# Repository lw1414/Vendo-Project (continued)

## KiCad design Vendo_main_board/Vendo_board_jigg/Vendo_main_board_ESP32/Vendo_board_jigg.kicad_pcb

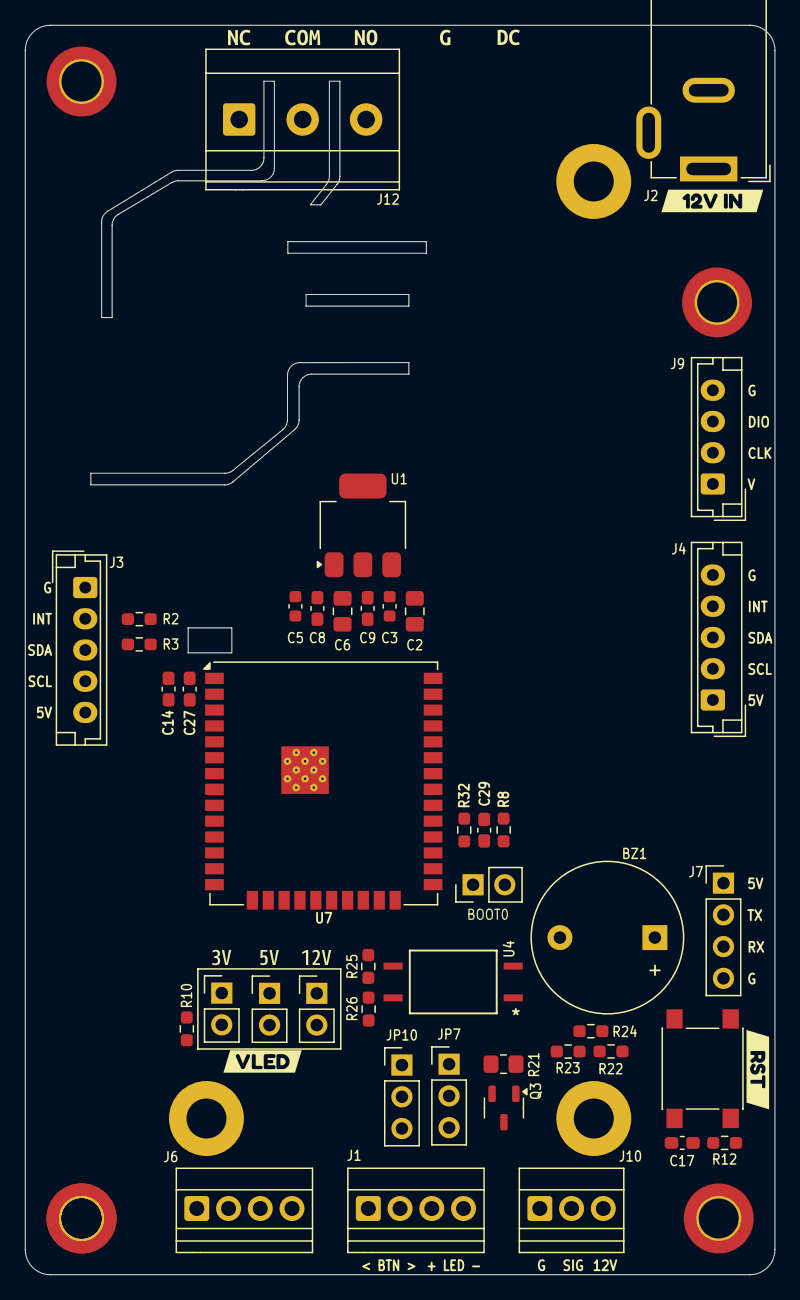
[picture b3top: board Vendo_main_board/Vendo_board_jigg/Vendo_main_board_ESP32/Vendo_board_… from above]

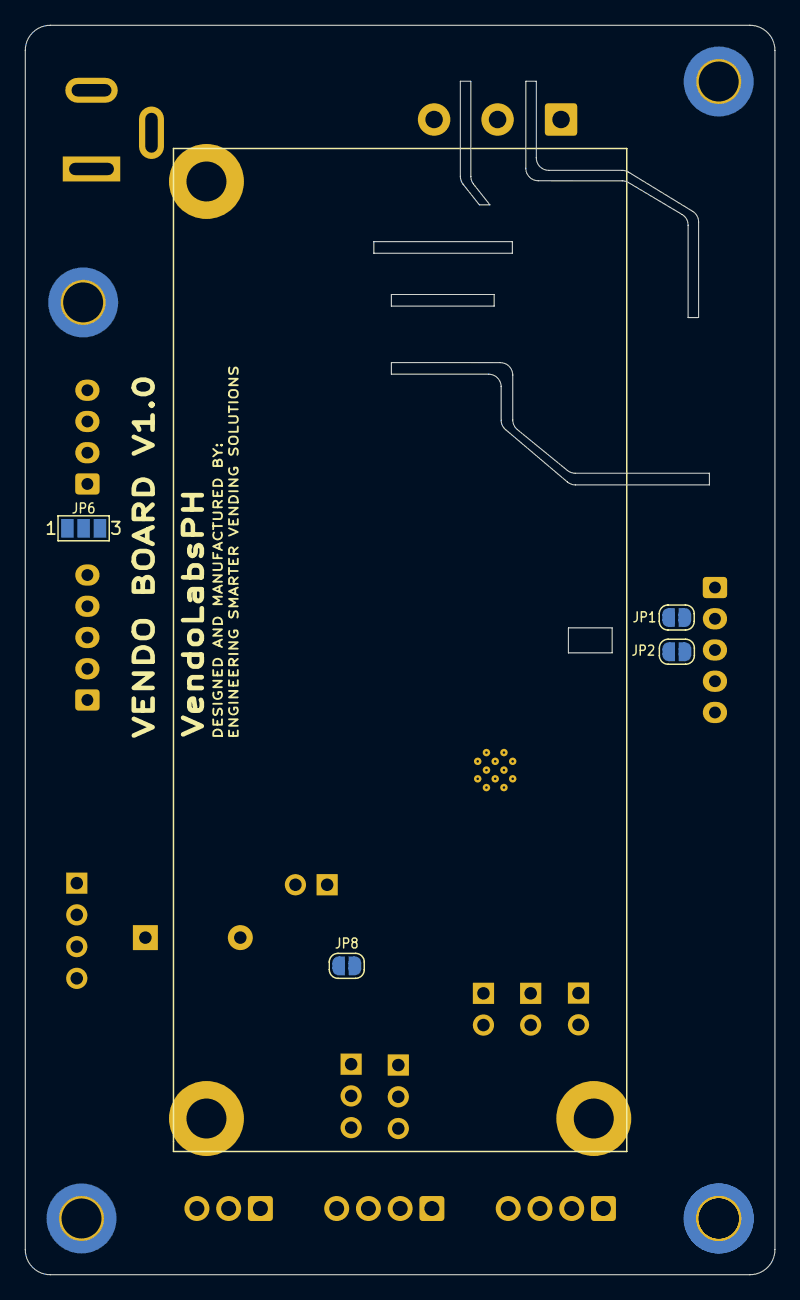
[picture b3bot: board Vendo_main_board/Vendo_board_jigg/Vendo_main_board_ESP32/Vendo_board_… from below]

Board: 2 copper layers, 60.0 x 100.0 mm, 63 parts (4 on the bottom side), 27 nets, no tracks yet.

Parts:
BZ1: Buzzer; Buzzer_12x9.5RM7.6
C2, C6: 1uF; C_0805_2012Metric_Pad1.18x1.45mm_HandSolder
C3, C5: 22uF; C_0603_1608Metric
C8, C27, C29: 100nF; C_0603_1608Metric_Pad1.08x0.95mm_HandSolder
C9: 10uF; C_0603_1608Metric_Pad1.08x0.95mm_HandSolder
C14: 22uF; C_0603_1608Metric_Pad1.08x0.95mm_HandSolder
C17: 1uF; C_0603_1608Metric_Pad1.08x0.95mm_HandSolder
H1, H2, H3, H4, H4#2: MountingHole; MountingHole_3.2mm_M3_DIN965_Pad_TopBottom
J1, J6: Screw_Terminal_01x04; TerminalBlock_Xinya_XY308-2.54-4P_1x04_P2.54mm_Horizontal
J2: Barrel_Jack_MountingPin; BarrelJack_GCT_DCJ200-10-A_Horizontal
J3, J4: Conn_01x05_Pin; JST_EH_B5B-EH-A_1x05_P2.50mm_Vertical
J7: FTDI; PinHeader_1x04_P2.54mm_Vertical
J9: Conn_01x04_Pin; JST_EH_B4B-EH-A_1x04_P2.50mm_Vertical
J10: Screw_Terminal_01x03; TerminalBlock_Xinya_XY308-2.54-3P_1x03_P2.54mm_Horizontal
J12: Screw_Terminal_01x03; TerminalBlock_MetzConnect_Type073_RT02603HBLU_1x03_P5.08mm_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
JP1, JP2, JP8: SolderJumper_2_Open; SolderJumper-2_P1.3mm_Open_RoundedPad1.0x1.5mm
JP3, JP4, JP5: SolderJumper_2_Open; PinHeader_1x02_P2.54mm_Vertical
JP6: SolderJumper_3_Open; SolderJumper-3_P1.3mm_Open_Pad1.0x1.5mm_NumberLabels
JP7, JP10: Jumper_3_Open; PinHeader_1x03_P2.54mm_Vertical
Q3: Q_NMOS_Depletion_GSD; SOT-23-3
R2, R3: 4.7K; R_0603_1608Metric_Pad0.98x0.95mm_HandSolder
R8, R12: 10K; R_0603_1608Metric_Pad0.98x0.95mm_HandSolder
R10, R22, R24, R25: 1K; R_0603_1608Metric_Pad0.98x0.95mm_HandSolder
R21: 10K; R_0805_2012Metric_Pad1.20x1.40mm_HandSolder
R23, R26: 1k; R_0603_1608Metric_Pad0.98x0.95mm_HandSolder
R32: 100K; R_0603_1608Metric_Pad0.98x0.95mm_HandSolder
SW1: SW_Push; SW_SPST_PTS645
SW7: SW_Push; PinHeader_1x02_P2.54mm_Vertical
U1: AMS1117-3.3; SOT-223-3_TabPin2
U4: PC817; APC-817xx-SL_AMB
U7: ESP32-WROOM-32; ESP32-WROOM-32UE
kibuzzard-6A0C4EC9: G***; kibuzzard-6A0C4EC9
kibuzzard-6A0C4ED1: G***; kibuzzard-6A0C4ED1
kibuzzard-6A0C4EDA: G***; kibuzzard-6A0C4EDA
kibuzzard-6A0C4EE4: G***; kibuzzard-6A0C4EE4
kibuzzard-6A0C5E83: G***; kibuzzard-6A0C5E83
kibuzzard-6A0C5E89: G***; kibuzzard-6A0C5E89
kibuzzard-6A0C5E92: G***; kibuzzard-6A0C5E92
kibuzzard-6A0C5F1E: G***; kibuzzard-6A0C5F1E
kibuzzard-6A0C536D: G***; kibuzzard-6A0C536D
kibuzzard-6A0C5003: G***; kibuzzard-6A0C5003
kibuzzard-6A563CE9: G***; kibuzzard-6A563CE9

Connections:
+3.3V: C5.2, C6.2, C8.2, C9.2, C14.1, C27.1, JP5.2 (B), JP6.1 (A), R2.1, R3.1, R8.1, R10.1, R12.1, R25.1, R32.1, U1.2 (VO), U7.2 (VDD)
+5V: BZ1.1 (+), C2.2, C3.2, J3.5, J4.1, J7.1, JP4.2 (B), JP6.3 (B), R22.1, U1.3 (VI)
+12V: J2.1, J10.3, JP3.2 (B)
AUX_1: J6.2, U7.8 (IO32)
AUX_2: J6.3, U7.9 (IO33)
COIN_EN: Q3.1 (G), R21.1, U7.14 (IO12)
COIN_IN: JP8.2 (B), R25.2, R26.2, U4.4, U7.28 (IO17)
ESP_EN: C17.2, R12.2, SW1.1, U7.3 (EN)
ESP_I0: R8.2, SW7.1, U7.25 (IO0)
ESP_RX: J7.3, U7.34 (RXD0/IO3)
ESP_SCL: J3.4, J4.2, JP1.1 (A), U7.36 (IO22)
ESP_SDA: J3.3, J4.3, JP2.1 (A), U7.33 (IO21)
ESP_TX: J7.2, U7.35 (TXD0/IO1)
GND: C2.1, C3.1, C5.1, C6.1, C8.1, C9.1, C14.2, C17.1, C27.2, C29.1, J1.2, J2.2, J3.1, J4.5, J6.4, J7.4, J9.4, JP7.1 (A), JP10.1 (A), Q3.2 (S), R21.2, R23.1, R26.1, SW1.2, SW7.2, U1.1 (GND), U4.2, U4.3, U7.1 (GND), U7.15 (GND), U7.38 (GND), U7.39 (GND)
I2C_CONFG: JP10.2 (C), U7.29 (IO5)
I2C_INT: C29.2, J3.2, J4.4, R32.2, U7.27 (IO16)
unnamed: J1.3, JP3.1 (A), JP4.1 (A), JP5.1 (A)
unnamed: J9.1, JP6.2 (C)
unnamed: J10.1, JP7.2 (C)
unnamed: J10.2, JP8.1 (A), R22.2, R23.2, R24.1
unnamed: JP1.2 (B), R2.2
unnamed: JP2.2 (B), R3.2
unnamed: JP7.3 (B), Q3.3 (D)
unnamed: R24.2, U4.1
SEG_CLK: J9.2, U7.16 (IO13)
SEG_DIO: J9.3, U7.13 (IO14)
USER_BTN: J1.1, R10.2, U7.30 (IO18)

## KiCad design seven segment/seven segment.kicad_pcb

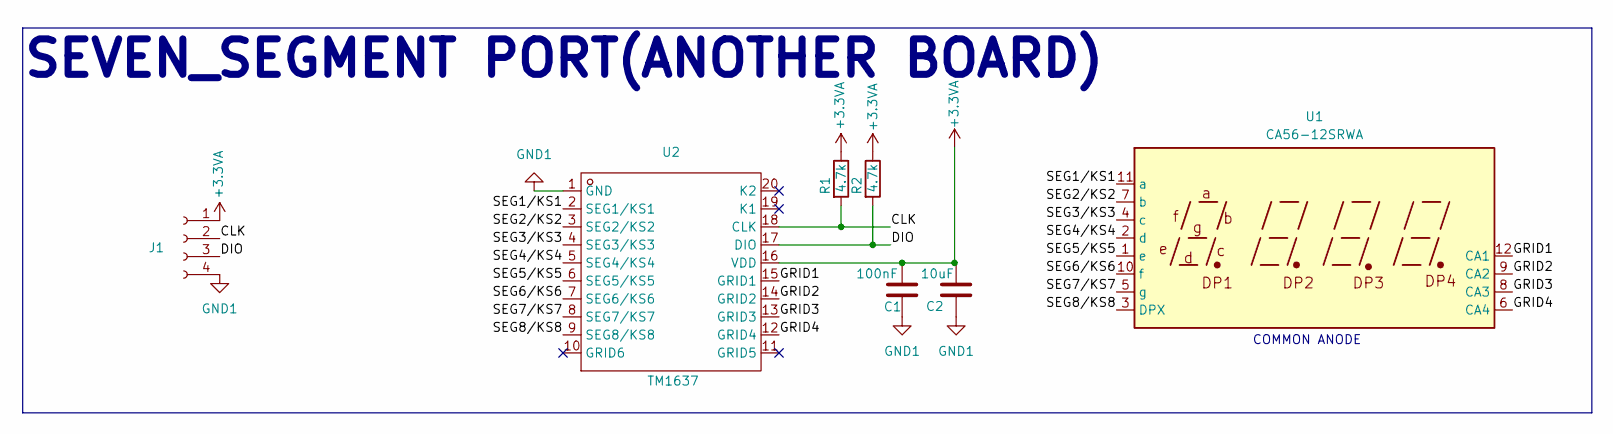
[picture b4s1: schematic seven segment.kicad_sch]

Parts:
C1: 100nF; C_0603_1608Metric_Pad1.08x0.95mm_HandSolder; LCSC C14663
C2: 10uF; C_0603_1608Metric_Pad1.08x0.95mm_HandSolder; LCSC C85713
J1: Conn_01x04_Socket; JST_EH_B4B-EH-A_1x04_P2.50mm_Vertical
R1, R2: 4.7k; R_0603_1608Metric_Pad0.98x0.95mm_HandSolder; LCSC C99782
U1: CA56-12SRWA
U2: TM1637; SOP-20_L12.8-W7.5-P1.27-LS10.4-BL; Manufacturer Part TM1637; LCSC Part Name LED驱动控制专用电路

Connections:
+3.3VA: C1.2, C2.2, J1.1, R1.1, R2.1, U2.16 (VDD)
/CLK: J1.2, R1.2, U2.18 (CLK)
/DIO: J1.3, R2.2, U2.17 (DIO)
/GRID1: U1.12 (CA1), U2.15 (GRID1)
/GRID2: U1.9 (CA2), U2.14 (GRID2)
/GRID3: U1.8 (CA3), U2.13 (GRID3)
/GRID4: U1.6 (CA4), U2.12 (GRID4)
/SEG1/KS1: U1.11 (a), U2.2 (SEG1/KS1)
/SEG2/KS2: U1.7 (b), U2.3 (SEG2/KS2)
/SEG3/KS3: U1.4 (c), U2.4 (SEG3/KS3)
/SEG4/KS4: U1.2 (d), U2.5 (SEG4/KS4)
/SEG5/KS5: U1.1 (e), U2.6 (SEG5/KS5)
/SEG6/KS6: U1.10 (f), U2.7 (SEG6/KS6)
/SEG7/KS7: U1.5 (g), U2.8 (SEG7/KS7)
/SEG8/KS8: U1.3 (DPX), U2.9 (SEG8/KS8)
GND1: C1.1, C2.1, J1.4, U2.1 (GND)

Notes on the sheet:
COMMON ANODE
SEVEN_SEGMENT PORT(ANOTHER BOARD)

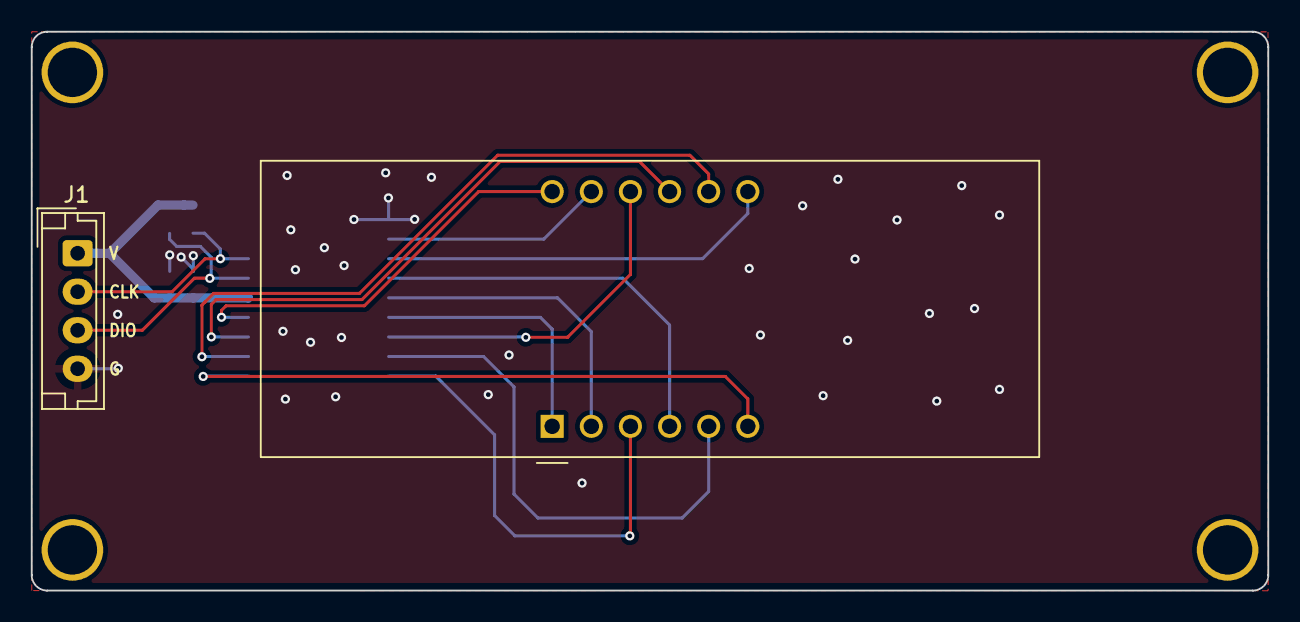
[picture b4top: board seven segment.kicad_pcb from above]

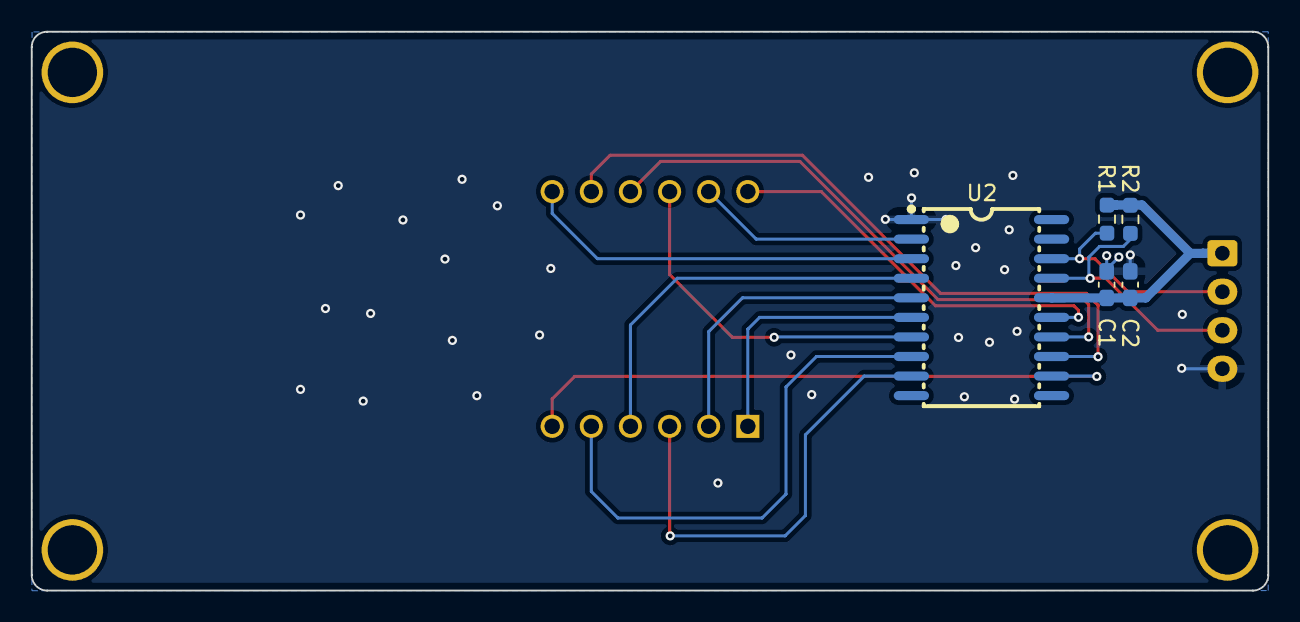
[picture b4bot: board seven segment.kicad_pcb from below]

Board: 2 copper layers, 80.3 x 36.3 mm, 7 parts (5 on the bottom side), 16 nets.

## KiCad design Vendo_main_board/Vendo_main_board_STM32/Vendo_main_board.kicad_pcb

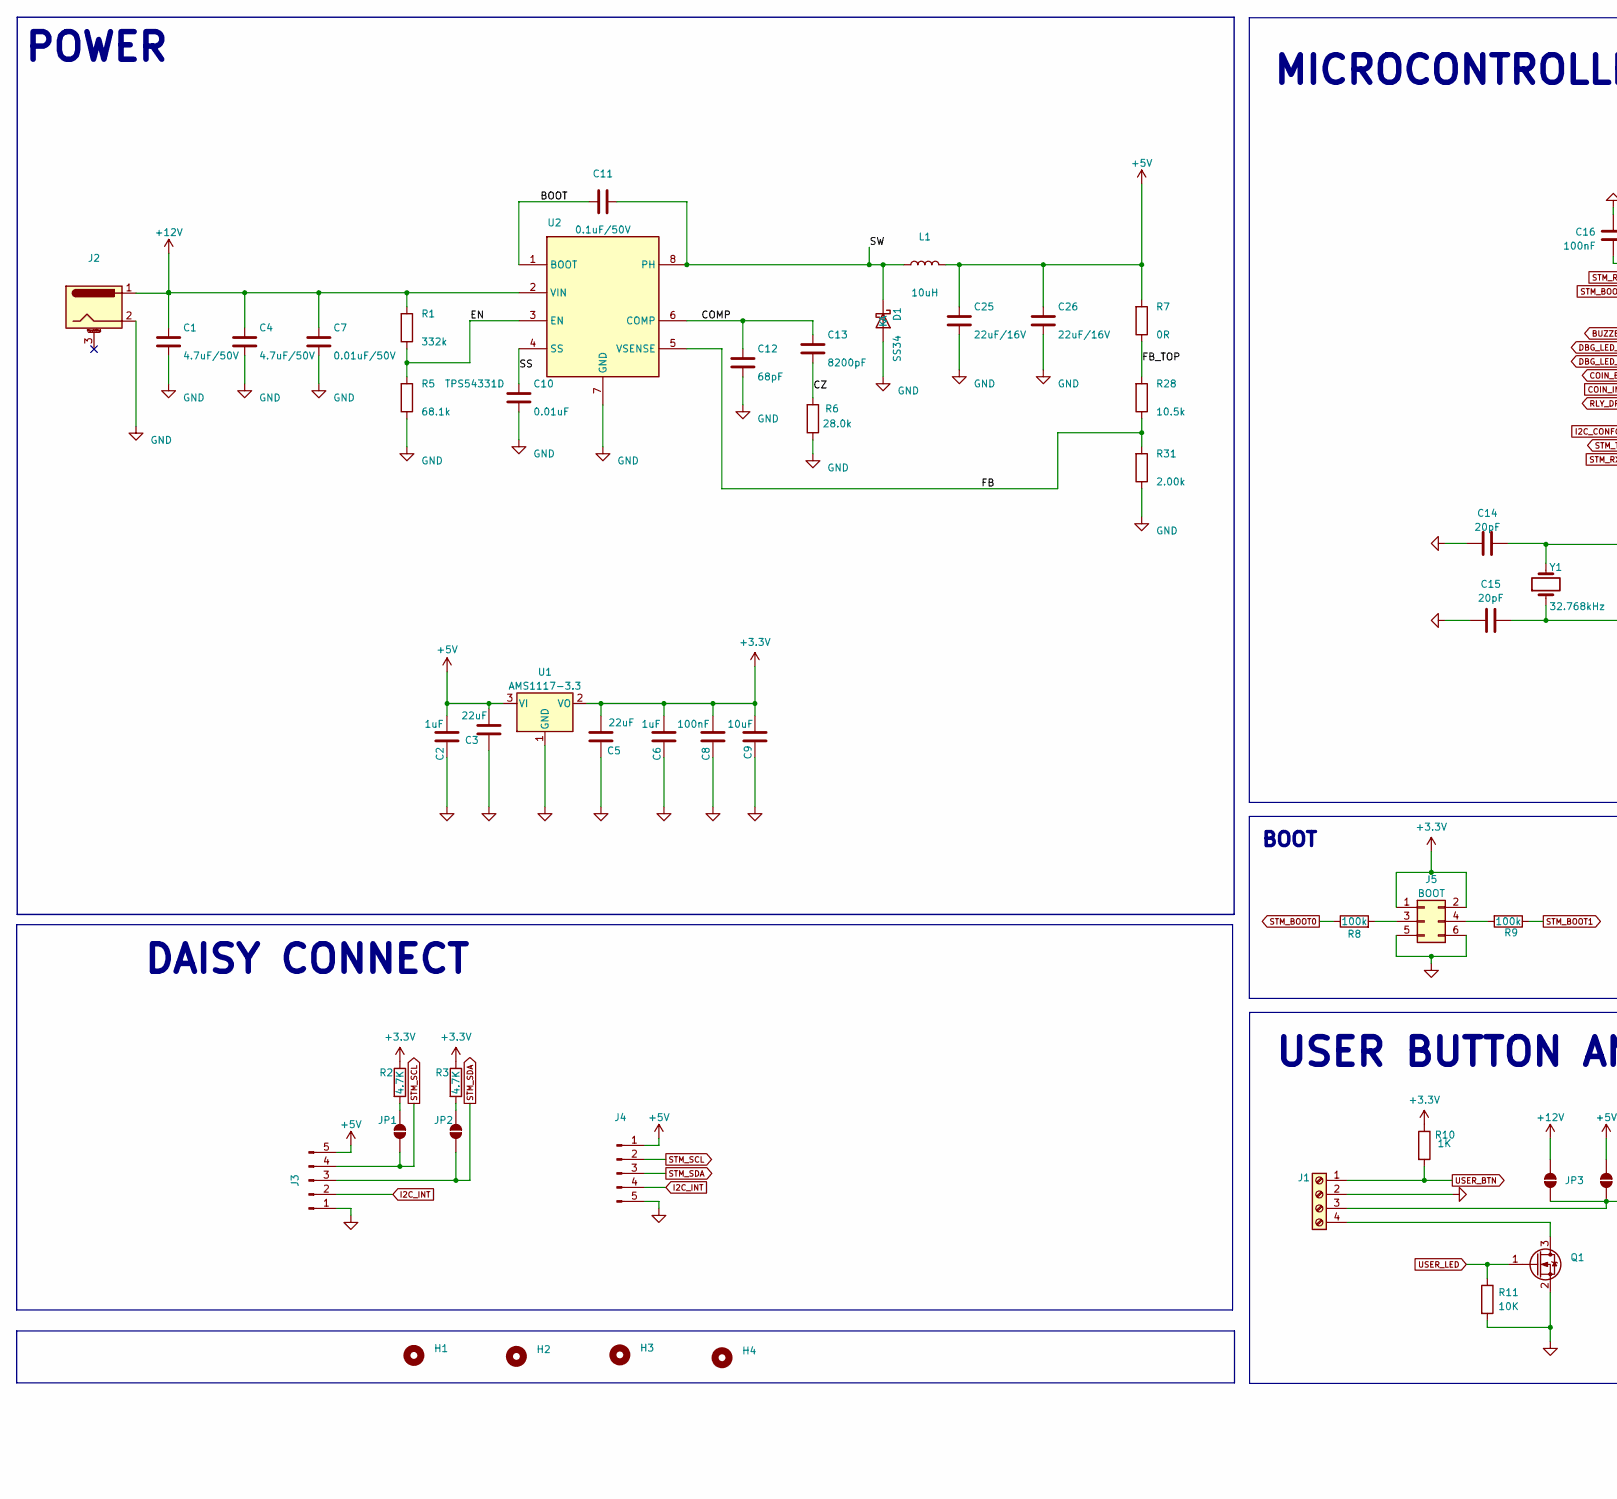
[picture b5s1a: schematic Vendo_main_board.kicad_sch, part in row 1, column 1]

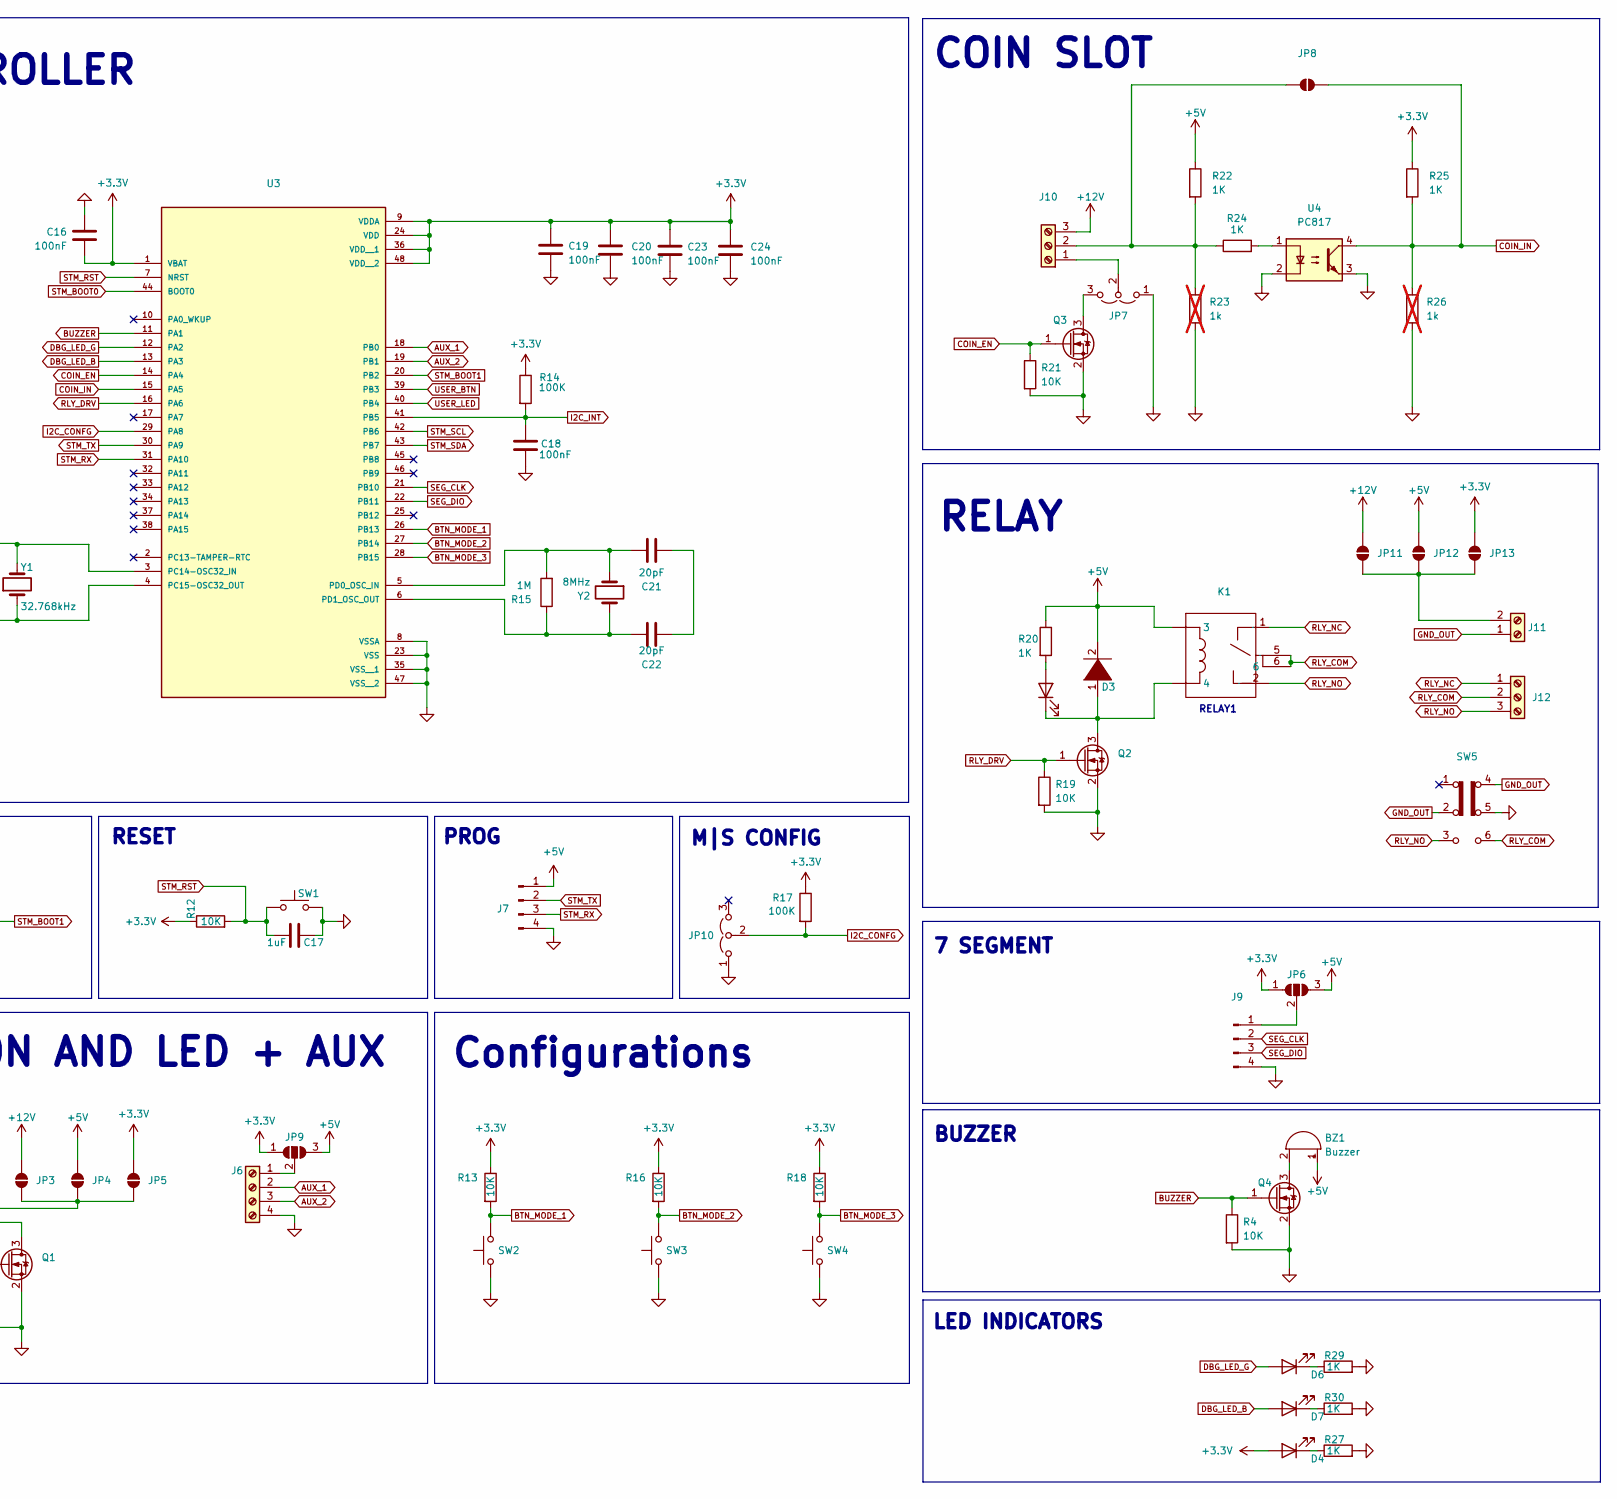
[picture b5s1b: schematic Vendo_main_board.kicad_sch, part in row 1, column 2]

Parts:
BZ1: Buzzer; Buzzer_12x9.5RM7.6
C1, C4: 4.7uF/50V; C_1206_3216Metric; MPN FH 1206B475K500NT; LCSC C29823
C2, C6: 1uF; C_0805_2012Metric_Pad1.18x1.45mm_HandSolder; LCSC C49678
C3, C5: 22uF; C_0603_1608Metric; LCSC C59461
C7: 0.01uF/50V; C_0603_1608Metric; MPN Samsung CL10B103KB8NNNC; LCSC C1589
C8, C16, C18, C19, C20, C23, C24: 100nF; C_0603_1608Metric_Pad1.08x0.95mm_HandSolder; LCSC C14663
C9: 10uF; C_0603_1608Metric_Pad1.08x0.95mm_HandSolder; LCSC C85713
C10: 0.01uF; C_0603_1608Metric; MPN Samsung CL10B103KB8NNNC; LCSC C1589
C11: 0.1uF/50V; C_0603_1608Metric; MPN Samsung CL10B104KB8NNNC; LCSC C1591
C12: 68pF; C_0603_1608Metric; MPN FH 0603CG680J500NT; LCSC C1680
C13: 8200pF; C_0603_1608Metric; MPN FH 0603B822K500NT; LCSC C1322360
C14, C15, C21, C22: 20pF; C_0603_1608Metric; LCSC C1648
C17: 1uF; C_0603_1608Metric_Pad1.08x0.95mm_HandSolder; LCSC C14663
C25, C26: 22uF/16V; C_1210_3225Metric; MPN Samsung CL32B226KOJNNNE; LCSC C55530
D1: SS34; D_SMA; MPN R+O SS34; LCSC C7420365
D2, D4, D6, D7: LED; LED_0805_2012Metric_Pad1.15x1.40mm_HandSolder; LCSC C2297
D3: 1N4001; D_SOD-123F; LCSC C2892326
H1, H2, H3, H4: MountingHole; MountingHole_3.2mm_M3_DIN965_Pad_TopBottom
J1, J6: Screw_Terminal_01x04; TerminalBlock_Xinya_XY308-2.54-4P_1x04_P2.54mm_Horizontal
J2: Barrel_Jack_MountingPin; BarrelJack_GCT_DCJ200-10-A_Horizontal
J3, J4: Conn_01x05_Pin; JST_EH_B5B-EH-A_1x05_P2.50mm_Vertical
J5: BOOT; PinSocket_2x03_P2.54mm_Vertical
J7: FTDI; PinHeader_1x04_P2.54mm_Vertical
J9: Conn_01x04_Pin; JST_EH_B4B-EH-A_1x04_P2.50mm_Vertical
J10: Screw_Terminal_01x03; TerminalBlock_Xinya_XY308-2.54-3P_1x03_P2.54mm_Horizontal
J11: Screw_Terminal_01x02; TerminalBlock_MetzConnect_Type073_RT02602HBLU_1x02_P5.08mm_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
J12: Screw_Terminal_01x03; TerminalBlock_MetzConnect_Type073_RT02603HBLU_1x03_P5.08mm_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
JP1, JP2, JP8: SolderJumper_2_Open; SolderJumper-2_P1.3mm_Open_RoundedPad1.0x1.5mm
JP3, JP4, JP5, JP11, JP12, JP13: SolderJumper_2_Open; PinHeader_1x02_P2.54mm_Vertical
JP6, JP9: SolderJumper_3_Open; SolderJumper-3_P1.3mm_Open_Pad1.0x1.5mm_NumberLabels
JP7, JP10: Jumper_3_Open; PinHeader_1x03_P2.54mm_Vertical
K1: RELAY-TH_SLA-XXVDC-SL-C; Manufacturer Part SLA-5VDC-SL-C; LCSC Part Name 5V继电器 单刀双掷
L1: 10uH; IND-SMD_L11.5-W10.0_FXL1040; MPN cjiang FXL1040-100-M; LCSC C475915
Q1, Q2, Q3, Q4: Q_NMOS_Depletion_GSD; SOT-23-3; LCSC C75882
R1: 332k; R_0603_1608Metric; MPN UNI-ROYAL 0603WAF3323T5E; LCSC C23139
R2, R3: 4.7K; R_0603_1608Metric_Pad0.98x0.95mm_HandSolder; LCSC C2960810
R4, R11, R19, R21: 10K; R_0805_2012Metric_Pad1.20x1.40mm_HandSolder; LCSC C2930231
R5: 68.1k; R_0603_1608Metric; MPN UNI-ROYAL 0603WAF6812T5E; LCSC C25976
R6: 28.0k; R_0603_1608Metric; MPN UNI-ROYAL 0603WAF2802T5E; LCSC C22989
R7: 0R; R_0603_1608Metric; MPN YAGEO RC0603JR-070RL; LCSC C95177
R8, R9: 100k; R_0603_1608Metric_Pad0.98x0.95mm_HandSolder; LCSC C14675
R10, R20, R22, R24, R25, R27, R29, R30: 1K; R_0603_1608Metric_Pad0.98x0.95mm_HandSolder; LCSC C21190
R12, R13, R16, R18: 10K; R_0603_1608Metric_Pad0.98x0.95mm_HandSolder; LCSC C21190
R14: 100K; R_0603_1608Metric_Pad0.98x0.95mm_HandSolder; LCSC C105574
R15: 1M; R_0603_1608Metric; LCSC C105578
R17: 100K; R_0603_1608Metric_Pad0.98x0.95mm_HandSolder; LCSC C21190
R23, R26: 1k; R_0603_1608Metric_Pad0.98x0.95mm_HandSolder; LCSC C21190; not fitted
R28: 10.5k; R_0603_1608Metric; MPN FOJAN FRC0603F1052TS; LCSC C2933127
R31: 2.00k; R_0603_1608Metric; MPN YAGEO RC0603FR-072KL; LCSC C105576
SW1: SW_Push; SW_SPST_PTS645; LCSC C2689642
SW2, SW3, SW4: SW_Push; SW_SPST_PTS645
SW5: SW_Slide_DPDT; DPDT_PUSH
U1: AMS1117-3.3; SOT-223-3_TabPin2; LCSC C5199435
U2: TPS54331D; SOIC-8_3.9x4.9mm_P1.27mm; MPN TPS54331DR; LCSC C9865
U3: STM32F103C8T6; LQFP-48_L7.0-W7.0-P0.50-LS9.0-BL; PARTREV 10; LCSC C8734
U4: PC817; APC-817xx-SL_AMB; LCSC C66405
Y1: 32.768kHz; OSC-SMD_L3.2-W1.5; LCSC C97606
Y2: 8MHz; HC-49S_L11.4-W4.9-LS13.4; LCSC C22379936

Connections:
+3.3V: C5.2, C6.2, C8.2, C9.2, C16.1, C19.2, C20.2, C23.2, C24.2, D4.2 (A), J5.1, J5.2, JP5.2 (B), JP6.1 (A), JP9.1 (A), JP13.2 (B), R2.1, R3.1, R10.1, R12.1, R13.1, R14.1, R16.1, R17.1, R18.1, R25.1, U1.2 (VO), U3.1 (VBAT), U3.9 (VDDA), U3.24 (VDD), U3.36 (VDD__1), U3.48 (VDD__2)
+5V: BZ1.1 (+), C2.2, C3.2, C25.1, C26.1, D3.2 (A), J3.5, J4.1, J7.1, JP4.2 (B), JP6.3 (B), JP9.3 (B), JP12.2 (B), K1.3, L1.2, R7.1, R20.1, R22.1, U1.3 (VI)
+12V: C1.1, C4.1, C7.1, J2.1, J10.3, JP3.2 (B), JP11.2 (B), R1.1, U2.2 (VIN)
/BOOT: C11.1, U2.1 (BOOT)
/COMP: C12.1, C13.1, U2.6 (COMP)
/CZ: C13.2, R6.1
/EN: R1.2, R5.1, U2.3 (EN)
/FB: R28.2, R31.1, U2.5 (VSENSE)
/FB_TOP: R7.2, R28.1
/SS: C10.1, U2.4 (SS)
/SW: C11.2, D1.1 (K), L1.1, U2.8 (PH)
AUX_1: J6.2, U3.18 (PB0)
AUX_2: J6.3, U3.19 (PB1)
BTN_MODE_1: R13.2, SW2.2, U3.26 (PB13)
BTN_MODE_2: R16.2, SW3.2, U3.27 (PB14)
BTN_MODE_3: R18.2, SW4.2, U3.28 (PB15)
BUZZER: Q4.1 (G), R4.1, U3.11 (PA1)
COIN_EN: Q3.1 (G), R21.1, U3.14 (PA4)
COIN_IN: JP8.2 (B), R25.2, R26.2, U3.15 (PA5), U4.4
DBG_LED_B: D7.2 (A), U3.13 (PA3)
DBG_LED_G: D6.2 (A), U3.12 (PA2)
GND: C1.2, C2.1, C3.1, C4.2, C5.1, C6.1, C7.2, C8.1, C9.1, C10.2, C12.2, C14.1, C15.1, C16.2, C17.1, C18.1, C19.1, C20.1, C23.1, C24.1, C25.2, C26.2, D1.2 (A), J1.2, J2.2, J3.1, J4.5, J5.5, J5.6, J6.4, J7.4, J9.4, JP7.1 (A), JP10.1 (A), Q1.2 (S), Q2.2 (S), Q3.2 (S), Q4.2 (S), R4.2, R5.2, R6.2, R11.2, R19.2, R21.2, R23.1, R26.1, R27.2, R29.2, R30.2, R31.2, SW1.2, SW2.1, SW3.1, SW4.1, SW5.5 (B), U1.1 (GND), U2.7 (GND), U3.8 (VSSA), U3.23 (VSS), U3.35 (VSS__1), U3.47 (VSS__2), U4.2, U4.3
GND_OUT: J11.1, SW5.2 (B), SW5.4 (C)
I2C_CONFG: JP10.2 (C), R17.2, U3.29 (PA8)
I2C_INT: C18.2, J3.2, J4.4, R14.2, U3.41 (PB5)
unnamed: BZ1.2 (-), Q4.3 (D)
unnamed: C21.1, C22.1
unnamed: D2.2 (A), R20.2
unnamed: D2.1 (K), D3.1 (K), K1.4, Q2.3 (D)
unnamed: D4.1 (K), R27.1
unnamed: D6.1 (K), R29.1
unnamed: D7.1 (K), R30.1
unnamed: J1.3, JP3.1 (A), JP4.1 (A), JP5.1 (A)
unnamed: J1.4, Q1.3 (D)
unnamed: J5.3, R8.2
unnamed: J5.4, R9.2
unnamed: J6.1, JP9.2 (C)
unnamed: J9.1, JP6.2 (C)
unnamed: J10.1, JP7.2 (C)
unnamed: J10.2, JP8.1 (A), R22.2, R23.2, R24.1
unnamed: J11.2, JP11.1 (A), JP12.1 (A), JP13.1 (A)
unnamed: JP1.2 (B), R2.2
unnamed: JP2.2 (B), R3.2
unnamed: JP7.3 (B), Q3.3 (D)
unnamed: R24.2, U4.1
unnamed: C14.2, U3.3 (PC14-OSC32_IN), Y1.2
unnamed: C15.2, U3.4 (PC15-OSC32_OUT), Y1.1
unnamed: C21.2, R15.2, U3.5 (PD0_OSC_IN), Y2.1
unnamed: C22.2, R15.1, U3.6 (PD1_OSC_OUT), Y2.2
RLY_COM: J12.2, K1.5, K1.6, SW5.6 (A)
RLY_DRV: Q2.1 (G), R19.1, U3.16 (PA6)
RLY_NC: J12.1, K1.1
RLY_NO: J12.3, K1.2, SW5.3 (C)
SEG_CLK: J9.2, U3.21 (PB10)
SEG_DIO: J9.3, U3.22 (PB11)
STM_BOOT0: R8.1, U3.44 (BOOT0)
STM_BOOT1: R9.1, U3.20 (PB2)
STM_RST: C17.2, R12.2, SW1.1, U3.7 (NRST)
STM_RX: J7.3, U3.31 (PA10)
STM_SCL: J3.4, J4.2, JP1.1 (A), U3.42 (PB6)
STM_SDA: J3.3, J4.3, JP2.1 (A), U3.43 (PB7)
STM_TX: J7.2, U3.30 (PA9)
USER_BTN: J1.1, R10.2, U3.39 (PB3)
USER_LED: Q1.1 (G), R11.1, U3.40 (PB4)

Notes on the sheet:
DAISY CONNECT
USER BUTTON AND LED + AUX
COIN SLOT
M|S CONFIG
RESET
POWER
7 SEGMENT
RELAY1
Configurations
PROG
RELAY
MICROCONTROLLER
BUZZER
BOOT
LED INDICATORS

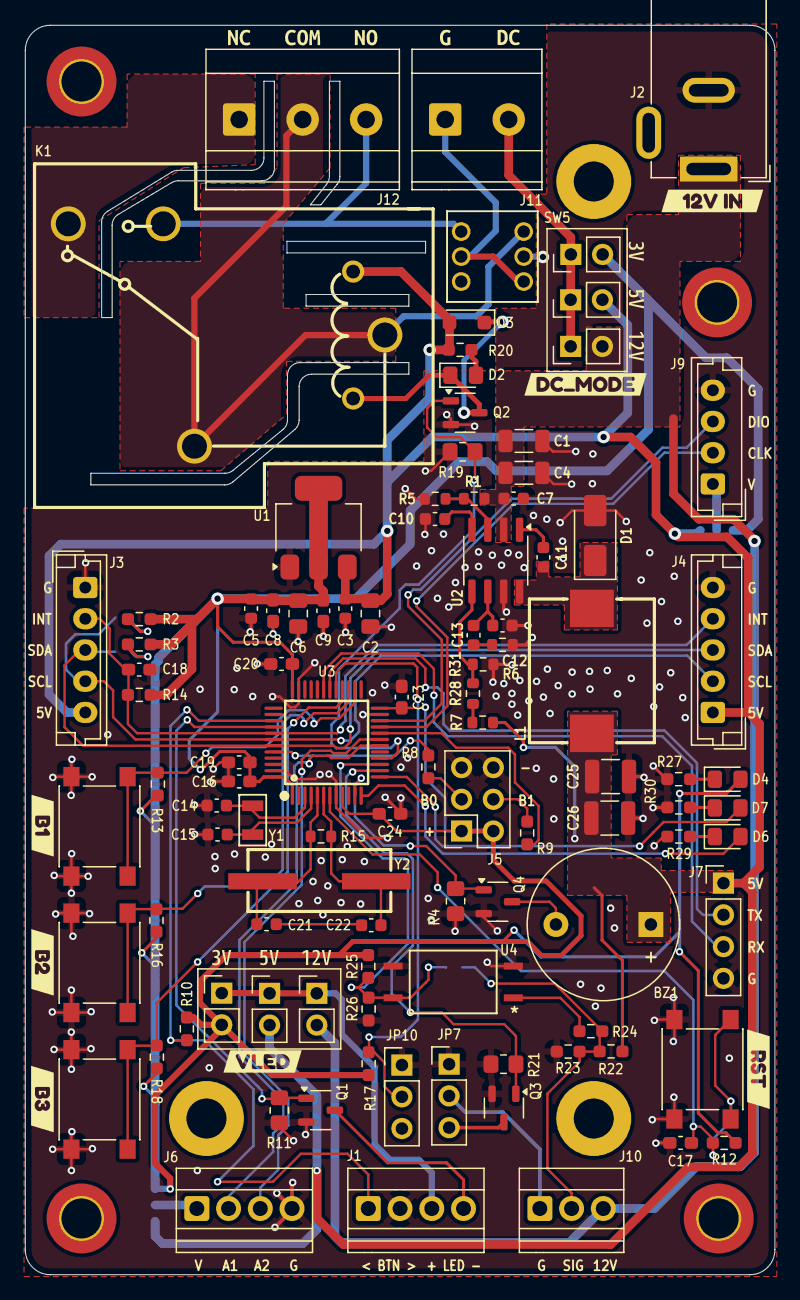
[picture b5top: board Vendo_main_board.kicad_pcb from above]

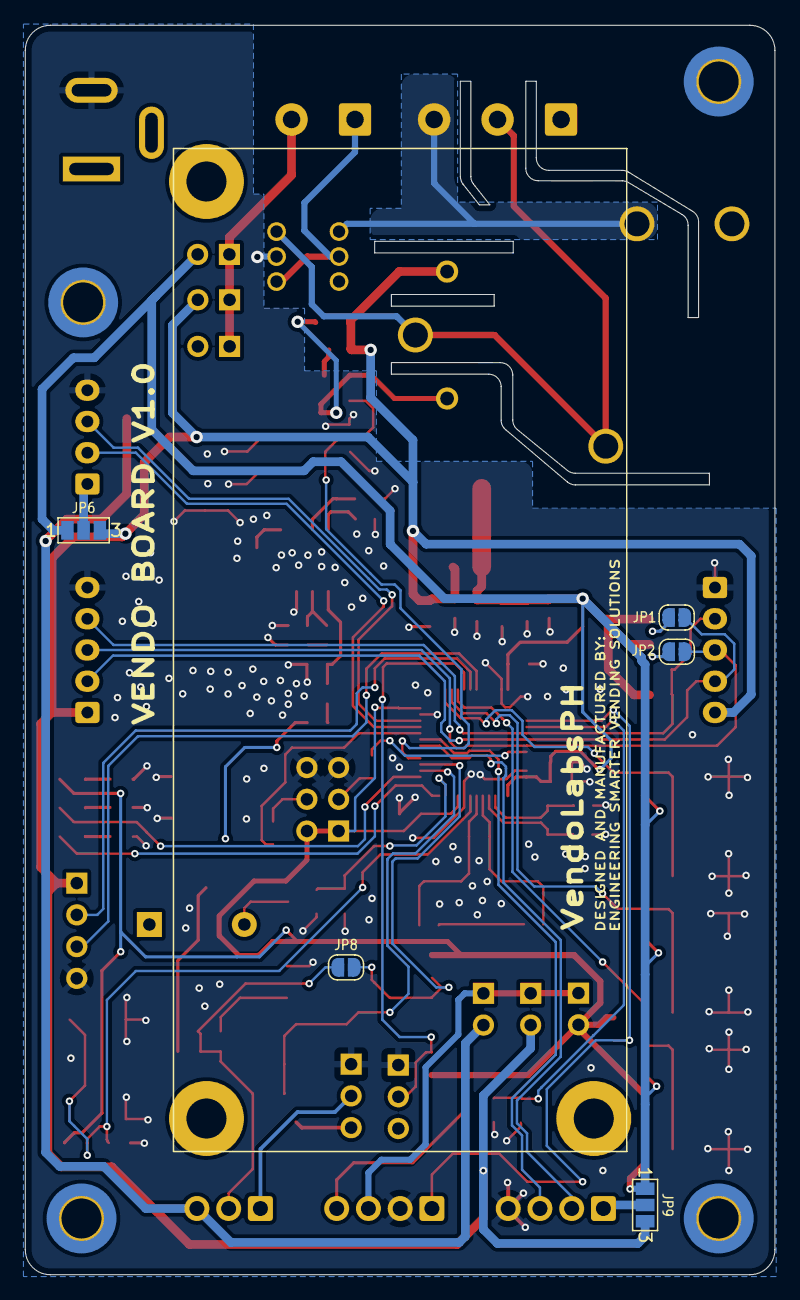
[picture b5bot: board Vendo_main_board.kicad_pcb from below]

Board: 2 copper layers, 60.0 x 100.0 mm, 127 parts (5 on the bottom side), 64 nets.

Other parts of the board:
kibuzzard-6A0C4EC9: G***; kibuzzard-6A0C4EC9
kibuzzard-6A0C4ED1: G***; kibuzzard-6A0C4ED1
kibuzzard-6A0C4EDA: G***; kibuzzard-6A0C4EDA
kibuzzard-6A0C4EE4: G***; kibuzzard-6A0C4EE4
kibuzzard-6A0C5E83, kibuzzard-6A0C5E83#2: G***; kibuzzard-6A0C5E83
kibuzzard-6A0C5E89, kibuzzard-6A0C5E89#2: G***; kibuzzard-6A0C5E89
kibuzzard-6A0C5E92, kibuzzard-6A0C5E92#2: G***; kibuzzard-6A0C5E92
kibuzzard-6A0C5F1E: G***; kibuzzard-6A0C5F1E
kibuzzard-6A0C57A3: G***; kibuzzard-6A0C57A3
kibuzzard-6A0C57A8: G***; kibuzzard-6A0C57A8
kibuzzard-6A0C57AC: G***; kibuzzard-6A0C57AC
kibuzzard-6A0C536D: G***; kibuzzard-6A0C536D
kibuzzard-6A0C5003: G***; kibuzzard-6A0C5003
kibuzzard-6A561C38: G***; kibuzzard-6A561C38
kibuzzard-6A563CE9: G***; kibuzzard-6A563CE9

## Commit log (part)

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2026-04-15 -update scheme
2026-04-26 -
    added load switch for 12V of coin slot
2026-05-04 -update schematic
    -recheck lcsc part number ,value
    -check and update footprint assignment
    -add load switch for the wdt and ldo combination
    -add link for quick connect footprint must be discuss for clarification
2026-05-07 -update scheme and pcb placement
    update scheme and footprint
    added spade connectors
2026-05-12 -update scheme for modular design
    -12V to 5V buck
    -5V isolation
    -3v3 ldo with wdt
    -STM32 blue pill
    -dip switch 8 pos with 74HC165
    -built in type C programmer
2026-05-13 -scheme edit and update
    Edits
    -Add 1x04(2.54mm pitch_)for programmer FTDI,STLINK and USB
    - coin slot terminal block footprint
    -jumper for optoclouper option for DNP
    -loadswitch for coin clot have jumper for DNP purposes
    -100k interrup value added
2026-05-13 -scheme edit
    -update lscs inductor and cap of iso
    -update footprint inductor
    -move esp_int on the jst pin
    -isolate the supply for the seven segment other boards
    -add 1x04 jst/ header for seven segment dio.clk and 3v3 supply
2026-05-14 -pcb , update scheme tweak
    -pcb placement
    -remove USB prog related , no need we have ftdi stlink
2026-05-19 -scheme update by charles
    1. Used standard input and output nodes
    2. Fixed GND connection of BOOT0 and BOOT1 (initially connected to Analog GND)
    3. Removed redundant 100K pull up WDT RST Pin
    4. Removed Nets on unconnected STM Pins
    5. Fixed GND of Oscillator
    6. Added 5V and 12V option to LED, removed LED as direct LED Drive
2026-05-19 -scheme minor edit -parts placement
    -remove 5VA to 5V , relay part and coin part
    -place components on the pcb for proposal
2026-05-19 -update schematic and placement
    -added buzzer
    -finalize pcb placement
2026-05-19 -pcb trace
    -pcb trace done
    -warnings is due to footprint default silk, and large silk can disregard
    -slit will be added
2026-05-20 -pcb additional
    -added slit for the relay
2026-05-20 -pcb minor edit
    -copper pour on nc,no and com for thick trace
    - via flood on regulator and buck
    - via stich for mcu side
    - thicker trace for 12V bottom part
2026-05-22 -repush
